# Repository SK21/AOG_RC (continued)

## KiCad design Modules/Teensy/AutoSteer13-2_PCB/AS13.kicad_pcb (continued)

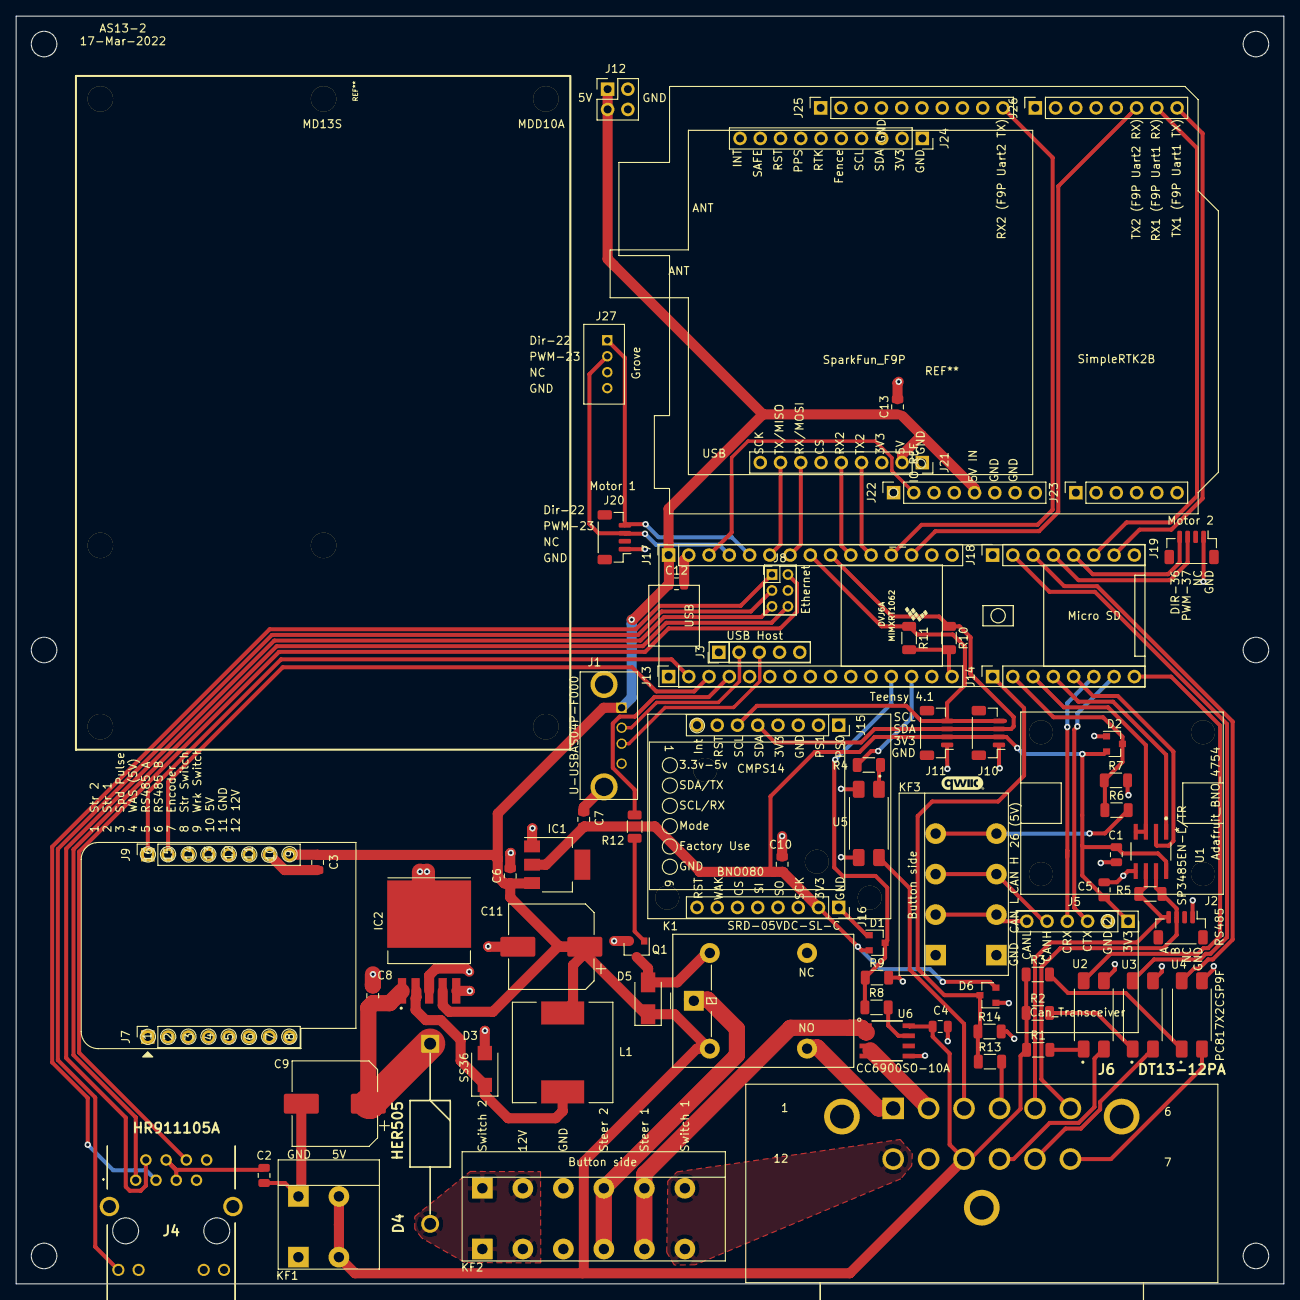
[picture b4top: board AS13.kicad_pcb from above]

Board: 2 copper layers, 159.0 x 159.0 mm, 82 parts (0 on the bottom side), 67 nets.

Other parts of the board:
  : MountingHole_3.2mm_M3
  #2,   #3,   #4,   #5,   #6: MountingHole_3.2mm_M3
--: Teensy 4.1; Teensy41_no_pins
M1: CMPS14; CMPS14_no_pins

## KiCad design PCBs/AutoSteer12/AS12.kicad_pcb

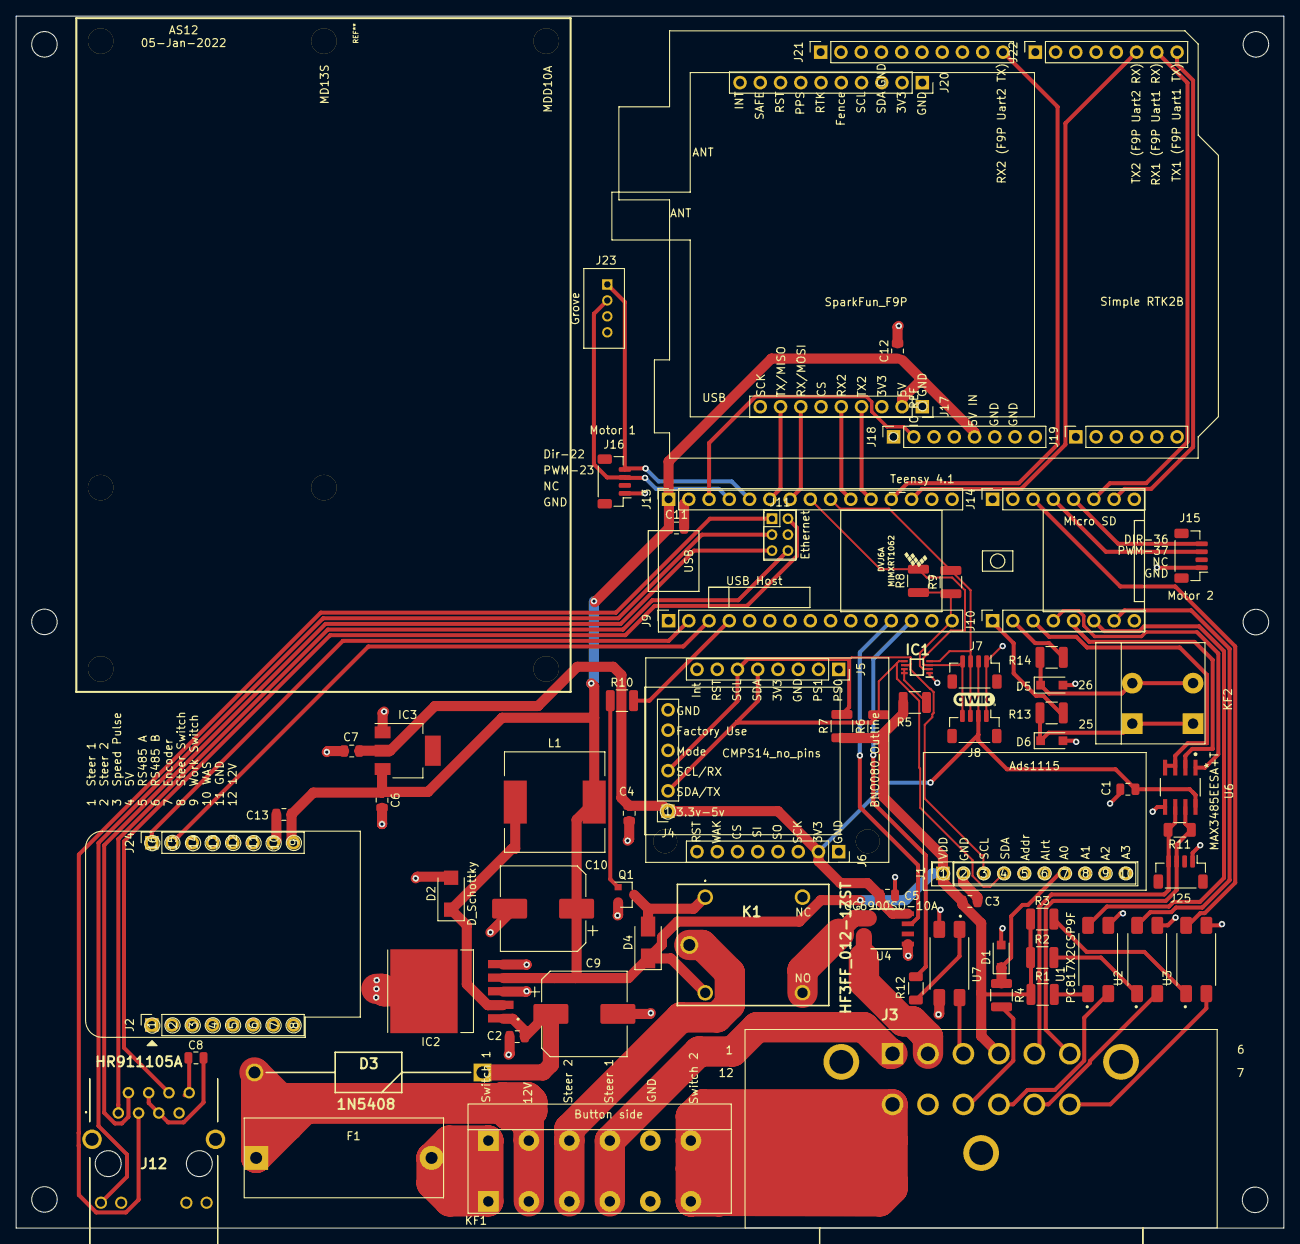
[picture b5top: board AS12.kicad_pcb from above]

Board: 2 copper layers, 159.0 x 152.0 mm, 81 parts (0 on the bottom side), 66 nets.

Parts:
 : MountingHole_3.2mm_M3
 #2,  #3,  #4,  #5,  #6: MountingHole_3.2mm_M3
--: Teensy 4.1; Teensy41_no_pins
C1, C3, C4, C5, C8, C11, C12, C13: 0.1uF; C_0805_2012Metric
C2: CL21B105KAFNNNE; C_0805_2012Metric
C6: 10uF; C_0805_2012Metric
C7: 22uF; C_0805_2012Metric
C9: RVT1V471M1010; CP_Elec_10x10.5
C10: RVT1V331M1010; CP_Elec_10x10.5
D1, D5, D6: Zener Diode; D_SOD-123F
D2: D_Schottky; SMA(DO-214AC)
D3: 1N5408; DO-201AD-28
D4: 1N4007; D_SMA
F1: Fuse; Fuse_Holder_C3131
IC1: PCA9306DCUR; SOP50P310X90-8N
IC2: XL2596; TO263-5L
IC3: AZ1117; SOT-223
J1: ADS1115; PinSocket_1x10_P2.54mm_Vertical
J2: WemosD1_left; PinSocket_1x08_P2.54mm_Vertical
J3: DT13-12PA; DT1312PA
J4: CMPS14; PinSocket_1x06_P2.54mm_Vertical
J5: BNO080_left; PinSocket_1x08_P2.54mm_Vertical
J6: BNO080_right; PinSocket_1x08_P2.54mm_Vertical
J7, J8: I2C-3V3; Qwic_vertical
J9, J13: Conn_01x15_Female; PinSocket_1x15_P2.54mm_Vertical
J10, J14: Conn_01x08_Female; PinSocket_1x08_P2.54mm_Vertical
J11: Teensy_Ethernet; PinHeader_2x03_P2.00mm_Vertical
J12: HR911105A
J15: Motor 2; Qwic_vertical
J16: Motor 1; Qwic_vertical
J17: SF_F9P_left; PinSocket_1x09_P2.54mm_Vertical
J18: ArduSimple_tl; PinSocket_1x08_P2.54mm_Vertical
J19: ArduSimple_bl; PinSocket_1x06_P2.54mm_Vertical
J20: SF_F9P_right; PinSocket_1x10_P2.54mm_Vertical
J21: ArduSimple_tr; PinSocket_1x10_P2.54mm_Vertical
J22: ArduSimple_br; PinSocket_1x08_P2.54mm_Vertical
J23: Grove
J24: WemosD1_right; PinSocket_1x08_P2.54mm_Vertical
J25: RS485; Qwic_vertical
K1: HF3FF_012-1ZST; HF3FF0121ZST
KF1: KF142V-5.0-6P; KF142V-5.08-6P
KF2: KF142V-5.0-2P; KF142V-5.08-2P
L1: SMDRI127-330MT; TMPA1265SP-101MN-D
M1: CMPS14_no_pins
Q1: BC847; SOT-23
R1, R2, R3, R4, R13, R14: 200; R_1210_3225Metric
R5: 200K; R_1210_3225Metric
R6, R7: 341; R_1210_3225Metric
R8, R9: 217; R_1210_3225Metric
R10: 1K; R_1210_3225Metric
R11: 120; R_1206_3216Metric
R12: 100; R_1206_3216Metric
U1, U2, U3, U7: PC817X2CSP9F; SOIC254P960X420-4N
U4: CC6900SO-10A; SOIC127P600X175-8N
U6: MAX3485EESA+T; Maxim_Integrated-S8-2-0-P-MFG

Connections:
GND: C1.2, C2.2, C3.2, C4.2, C5.2, C6.2, C7.2, C8.2, C9.2, C10.2, C11.2, C12.2, C13.2, D1.2, D2.2, D5.2, D6.2, IC1.1, IC2.3, IC2.5, IC2.6, IC3.1, J1.2, J1.5, J3.11, J4.6, J6.1, J7.1, J8.1, J9.1, J11.4, J12.8, J12.10, J13.2, J13.15, J15.1, J16.1, J17.1, J18.6, J18.7, J21.4, J23.4, J24.7, J25.1, KF1.5, Q1.2, U1.3, U2.3, U3.3, U4.5, U6.5, U7.2, U7.3
unnamed: C1.1, C4.1, C5.1, C7.1, IC3.2, J4.1, J6.2, J7.2, J8.2, U4.8, U6.8
unnamed: C2.1, C9.1, D3.1, IC2.1
unnamed: C8.1, J12.4, J12.5
unnamed: C3.1, C6.1, C10.1, C11.1, C12.1, C13.1, D4.1, IC2.4, IC3.3, J1.1, J3.4, J13.1, J17.2, J18.5, J24.8, K1.3, L1.2, R1.1, R2.1, R3.1, R5.1, R6.1, R7.1
unnamed: D1.1, J1.7, R4.1
unnamed: D2.1, IC2.2, L1.1
unnamed: D3.2, F1.1, KF1.2
unnamed: D4.2, K1.1, Q1.3
unnamed: D5.1, KF2.2, R14.1
unnamed: D6.1, KF2.1, R13.1
unnamed: F1.2, KF1.1
unnamed: IC1.2, J9.15, R8.1, R9.1
unnamed: IC1.3, J7.4, J8.4, J13.8, R8.2
unnamed: IC1.4, J7.3, J8.3, J13.9, R9.2
unnamed: IC1.5, J1.4, J4.2, J5.5, R6.2
unnamed: IC1.6, J1.3, J4.3, J5.6, R7.2
unnamed: IC1.7, IC1.8, R5.2
unnamed: J3.1, KF1.4
unnamed: J3.2, U4.3, U4.4
unnamed: J3.3, U7.4
unnamed: J3.7, U3.2
unnamed: J3.8, U2.2
unnamed: J3.9, U1.2
unnamed: J3.10, R4.2
unnamed: J3.12, KF1.6
unnamed: J9.4, R10.2
unnamed: J9.12, U4.7
unnamed: J9.13, R12.1
unnamed: J10.1, R13.2
unnamed: J10.2, R14.2
unnamed: J10.3, U6.3, U6.4
unnamed: J10.4, U6.1
unnamed: J10.5, U6.2
unnamed: J10.6, U1.4
unnamed: J10.7, U2.4
unnamed: J11.1, J12.3
unnamed: J11.2, J12.6
unnamed: J11.3, J12.9
unnamed: J11.5, J12.2
unnamed: J11.6, J12.1
unnamed: J13.3, J18.2
unnamed: J13.4, J16.3, J23.2
unnamed: J13.5, J16.4, J23.1
unnamed: J13.6, J17.8
unnamed: J13.7, J17.7
unnamed: J13.10, J17.5
unnamed: J13.11, J17.4
unnamed: J13.12, J21.10
unnamed: J13.13, J22.6
unnamed: J14.3, U3.4
unnamed: J14.4, J15.3
unnamed: J14.5, J15.4
unnamed: J14.6, J22.7
unnamed: J14.7, J22.8
unnamed: J9.2, J24.1
unnamed: J9.3, J24.2
unnamed: J3.6, J25.3, R11.1, U6.7
unnamed: J3.5, J25.4, R11.2, U6.6
unnamed: K1.2, KF1.3
unnamed: K1.4, U4.1, U4.2
unnamed: Q1.1, R10.1
unnamed: R1.2, U1.1
unnamed: R2.2, U2.1
unnamed: R3.2, U3.1
unnamed: R12.2, U7.1

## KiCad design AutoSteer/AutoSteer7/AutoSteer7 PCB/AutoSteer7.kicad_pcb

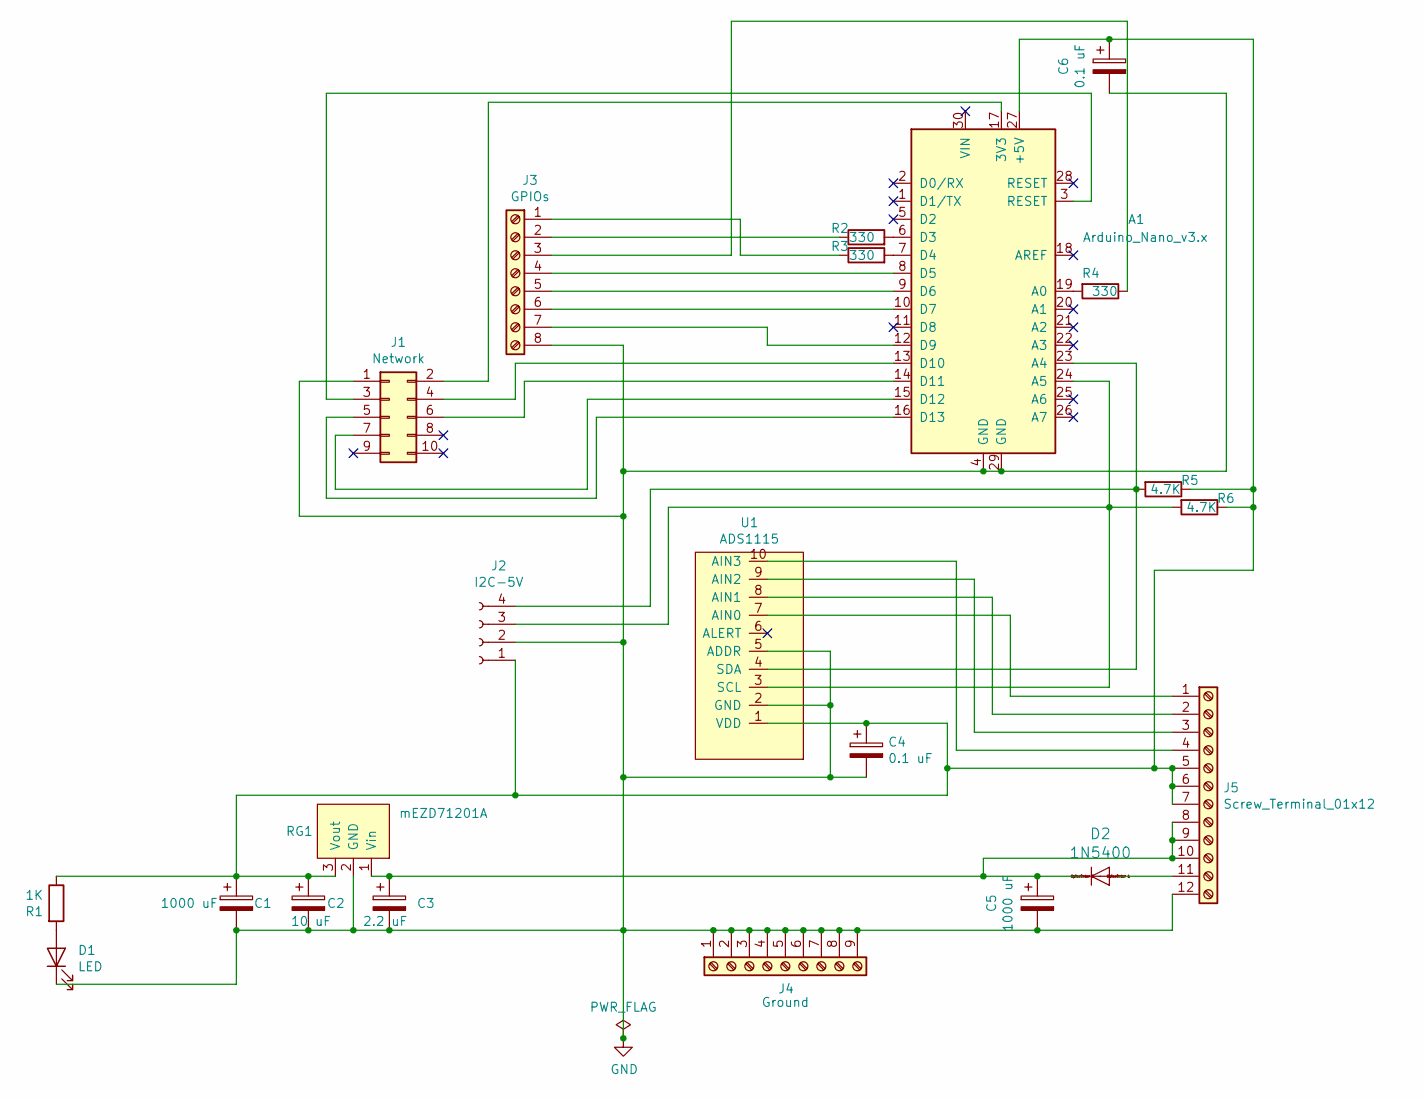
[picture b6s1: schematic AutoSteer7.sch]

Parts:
A1: Arduino_Nano_v3.x; Arduino_Nano
C1, C5: 1000 uF; CP_Radial_D10.0mm_P5.00mm
C2: 10 uF; C_Disc_D5.0mm_W2.5mm_P2.50mm
C3: 2.2 uF; C_Disc_D5.0mm_W2.5mm_P2.50mm
C4, C6: 0.1 uF; C_Disc_D5.0mm_W2.5mm_P2.50mm
D1: LED; LED_D3.0mm
D2: 1N5400
J1: Network; PinSocket_2x05_P2.54mm_Vertical
J2: I2C-5V; PinSocket_1x04_P2.54mm_Vertical
J3: GPIOs; TerminalBlock_Phoenix_PT-1,5-8-5.0-H_1x08_P5.00mm_Horizontal
J4: Ground; TerminalBlock_Phoenix_PT-1,5-9-5.0-H_1x09_P5.00mm_55degrees
J5: Screw_Terminal_01x12; TerminalBlock_Phoenix_PT-1,5-12-5.0-H_1x12_P5.00mm_Horizont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
R1: 1K; R_Axial_DIN0207_L6.3mm_D2.5mm_P10.16mm_Horizontal
R2, R3, R4: 330; R_Axial_DIN0207_L6.3mm_D2.5mm_P10.16mm_Horizontal
R5, R6: 4.7K; R_Axial_DIN0207_L6.3mm_D2.5mm_P10.16mm_Horizontal
RG1: mEZD71201A
U1: ADS1115; ads1115

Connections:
GND: A1.4 (GND), A1.29 (GND), C1.2, C2.2, C3.2, C4.2, C5.2, C6.2, D1.1 (K), J1.1, J2.2, J3.8, J4.1, J4.2, J4.3, J4.4, J4.5, J4.6, J4.7, J4.8, J4.9, J5.12, RG1.2 (GND), U1.2 (GND), U1.5 (ADDR)
unnamed: A1.3 (RESET), J1.3
unnamed: A1.6 (D3), R2.2
unnamed: A1.7 (D4), R3.2
unnamed: A1.8 (D5), J3.4
unnamed: A1.9 (D6), J3.5
unnamed: A1.10 (D7), J3.6
unnamed: A1.12 (D9), J3.7
unnamed: A1.13 (D10), J1.4
unnamed: A1.14 (D11), J1.6
unnamed: A1.15 (D12), J1.7
unnamed: A1.16 (D13), J1.5
unnamed: A1.17 (3V3), J1.2
unnamed: A1.19 (A0), R4.2
unnamed: A1.23 (A4), J2.4, R5.2, U1.4 (SDA)
unnamed: A1.24 (A5), J2.3, R6.2, U1.3 (SCL)
unnamed: A1.27 (+5V), C1.1, C2.1, C4.1, C6.1, J2.1, J5.5, J5.6, J5.7, R1.1, R5.1, R6.1, RG1.3 (Vout), U1.1 (VDD)
unnamed: C3.1, C5.1, D2.C, J5.8, J5.9, J5.10, RG1.1 (Vin)
unnamed: D1.2 (A), R1.2
unnamed: D2.A, J5.11
unnamed: J3.1, R3.1
unnamed: J3.2, R2.1
unnamed: J3.3, R4.1
unnamed: J5.1, U1.7 (AIN0)
unnamed: J5.2, U1.8 (AIN1)
unnamed: J5.3, U1.9 (AIN2)
unnamed: J5.4, U1.10 (AIN3)

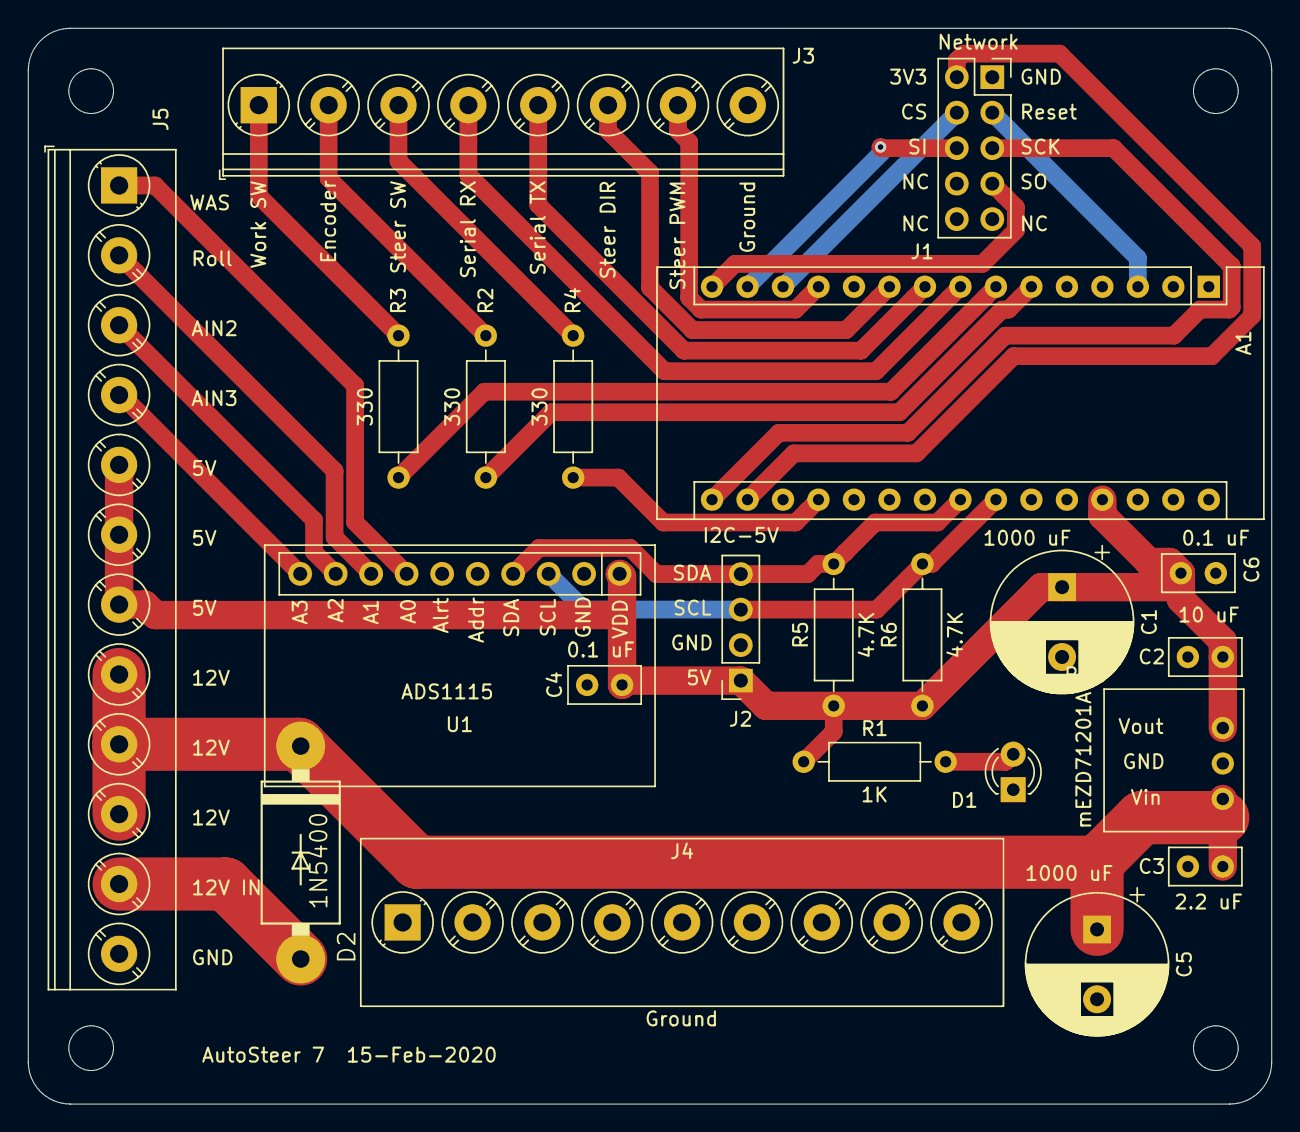
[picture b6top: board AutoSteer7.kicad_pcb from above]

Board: 2 copper layers, 89.0 x 77.0 mm, 22 parts (0 on the bottom side), 27 nets.

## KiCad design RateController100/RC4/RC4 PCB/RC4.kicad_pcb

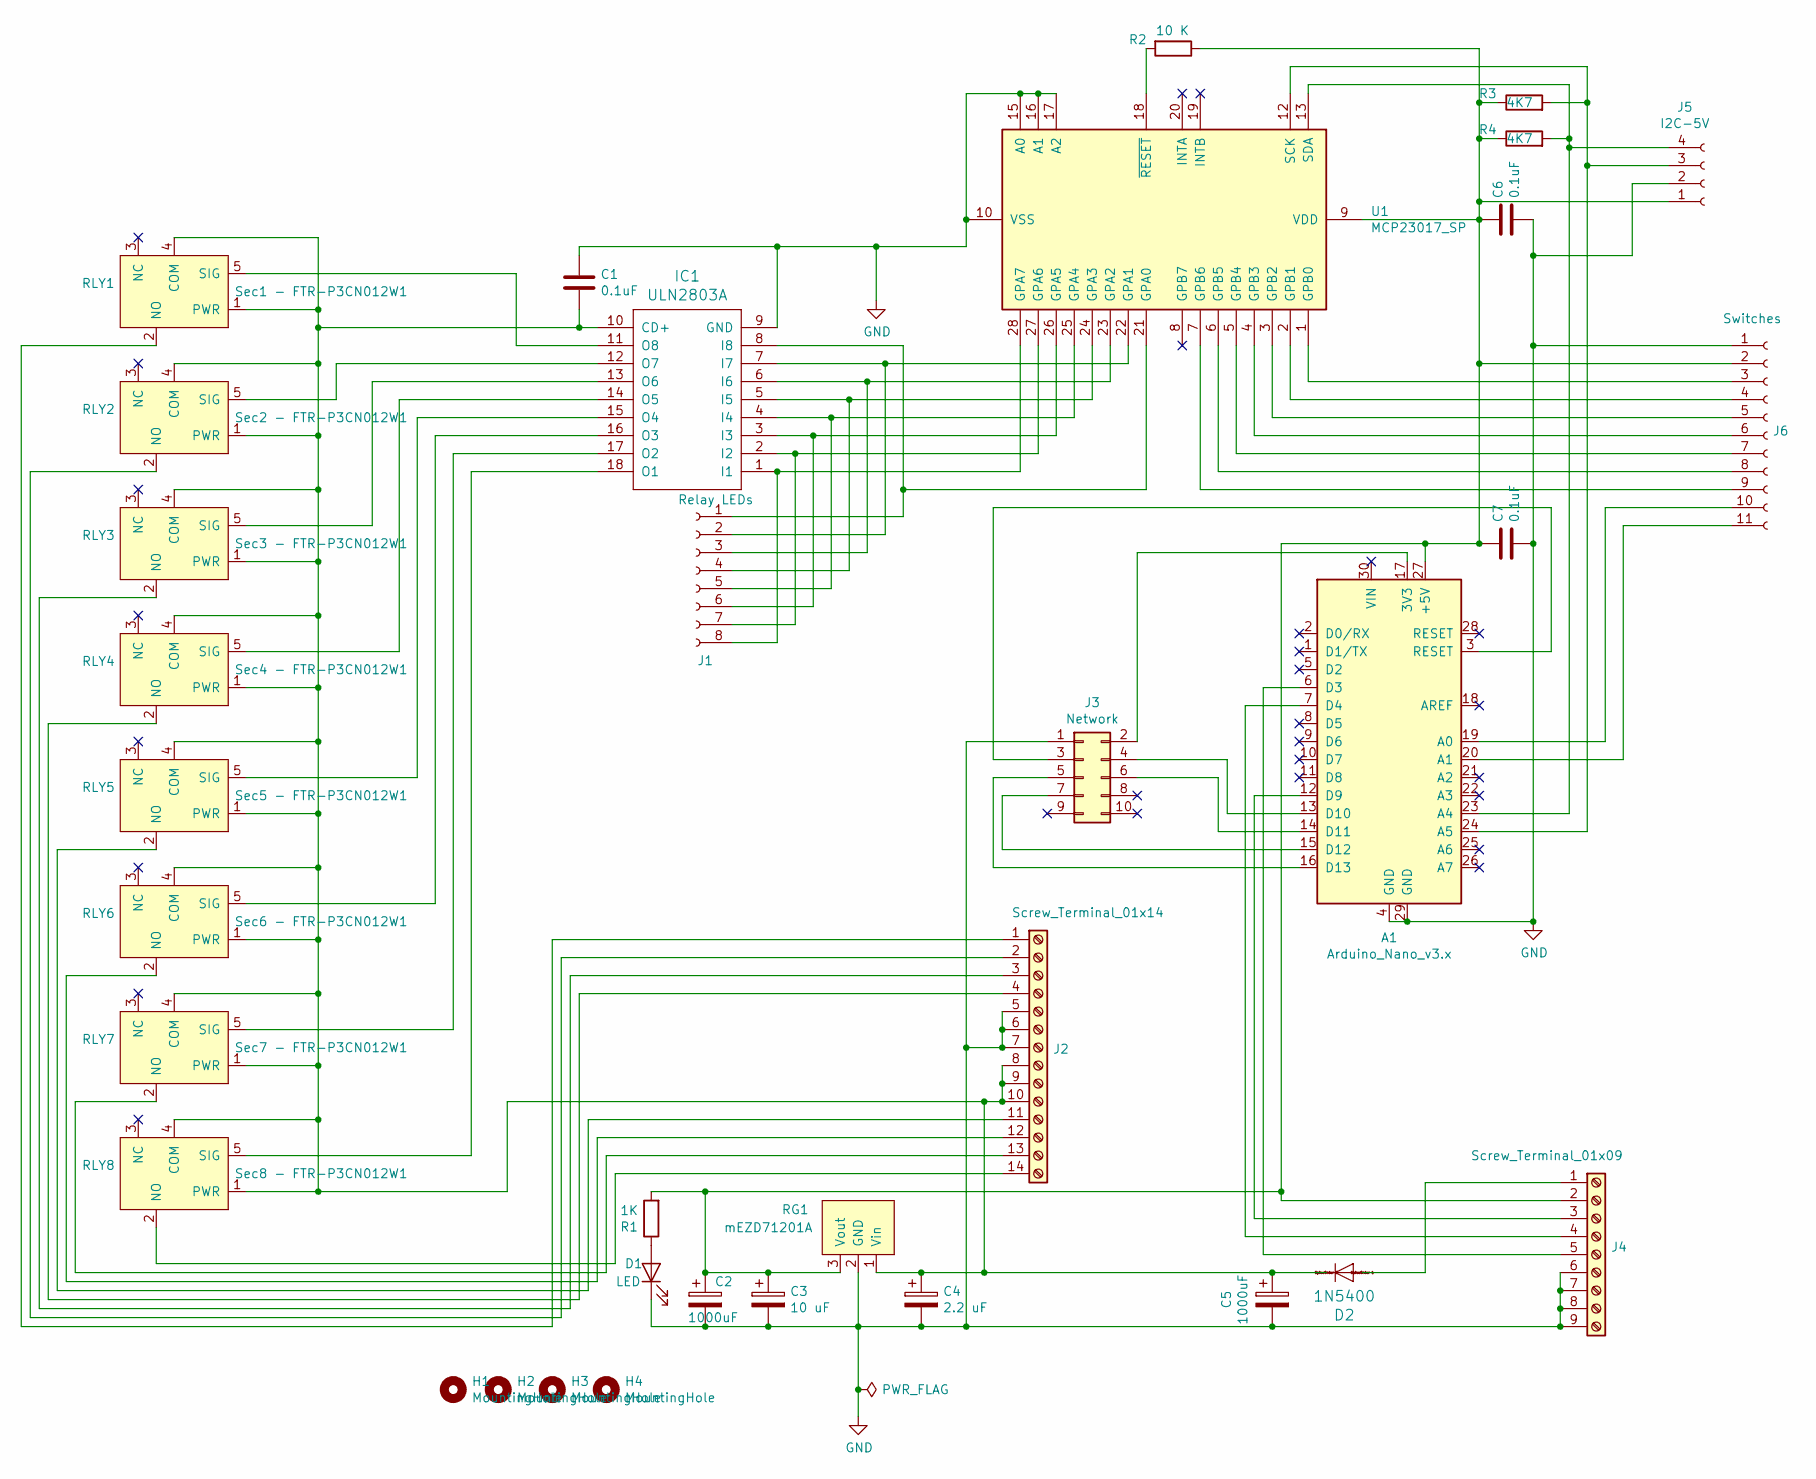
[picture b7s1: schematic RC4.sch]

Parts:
A1: Arduino_Nano_v3.x; Arduino_Nano
C1, C6, C7: 0.1uF; C_Disc_D5.0mm_W2.5mm_P2.50mm
C2, C5: 1000uF; CP_Radial_D10.0mm_P5.00mm
C3: 10 uF; C_Disc_D5.0mm_W2.5mm_P2.50mm
C4: 2.2 uF; C_Disc_D5.0mm_W2.5mm_P2.50mm
D1: LED; LED_D3.0mm
D2: 1N5400
H1, H2, H3, H4: MountingHole; MountingHole_3.2mm_M3
IC1: ULN2803A; DIL18
J1: Relay LEDs; PinHeader_1x08_P2.54mm_Vertical
J2: Screw_Terminal_01x14; TerminalBlock_Phoenix_MKDS-1,5-14_1x14_P5.00mm_Horizontal
J3: Network; PinSocket_2x05_P2.54mm_Vertical
J4: Screw_Terminal_01x09; TerminalBlock_Phoenix_PT-1,5-9-5.0-H_1x09_P5.00mm_Horizontal
J5: I2C-5V; PinSocket_1x04_P2.54mm_Vertical
J6: Switches; PinHeader_1x11_P2.54mm_Vertical
R1: 1K; R_Axial_DIN0207_L6.3mm_D2.5mm_P10.16mm_Horizontal
R2: 10 K; R_Axial_DIN0207_L6.3mm_D2.5mm_P10.16mm_Horizontal
R3, R4: 4K7; R_Axial_DIN0207_L6.3mm_D2.5mm_P10.16mm_Horizontal
RG1: mEZD71201A
RLY1: Sec1 - FTR-P3CN012W1; FTR-P3_Relay
RLY2: Sec2 - FTR-P3CN012W1; FTR-P3_Relay
RLY3: Sec3 - FTR-P3CN012W1; FTR-P3_Relay
RLY4: Sec4 - FTR-P3CN012W1; FTR-P3_Relay
RLY5: Sec5 - FTR-P3CN012W1; FTR-P3_Relay
RLY6: Sec6 - FTR-P3CN012W1; FTR-P3_Relay
RLY7: Sec7 - FTR-P3CN012W1; FTR-P3_Relay
RLY8: Sec8 - FTR-P3CN012W1; FTR-P3_Relay
U1: MCP23017_SP; DIP-28_W7.62mm

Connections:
GND: A1.4 (GND), A1.29 (GND), C1.1, C2.2, C3.2, C4.2, C5.2, C6.2, C7.2, D1.1 (K), IC1.9 (GND), J2.5, J2.6, J2.7, J3.1, J4.6, J4.7, J4.8, J4.9, J5.2, J6.1, RG1.2 (GND), U1.10 (VSS), U1.15 (A0), U1.16 (A1), U1.17 (A2)
unnamed: A1.3 (RESET), J3.3
unnamed: A1.6 (D3), J4.5
unnamed: A1.7 (D4), J4.4
unnamed: A1.12 (D9), J4.3
unnamed: A1.13 (D10), J3.4
unnamed: A1.14 (D11), J3.6
unnamed: A1.15 (D12), J3.7
unnamed: A1.16 (D13), J3.5
unnamed: A1.17 (3V3), J3.2
unnamed: A1.19 (A0), J6.10
unnamed: A1.20 (A1), J6.11
unnamed: A1.23 (A4), J5.4, R4.2, U1.13 (SDA)
unnamed: A1.24 (A5), J5.3, R3.2, U1.12 (SCK)
unnamed: A1.27 (+5V), C2.1, C3.1, C6.1, C7.1, J4.2, J5.1, J6.2, R1.2, R2.1, R3.1, R4.1, RG1.3 (Vout), U1.9 (VDD)
unnamed: C1.2, C4.1, C5.1, D2.C, IC1.10 (CD+), J2.8, J2.9, J2.10, RG1.1 (Vin), RLY1.1 (PWR), RLY1.4 (COM), RLY2.1 (PWR), RLY2.4 (COM), RLY3.1 (PWR), RLY3.4 (COM), RLY4.1 (PWR), RLY4.4 (COM), RLY5.1 (PWR), RLY5.4 (COM), RLY6.1 (PWR), RLY6.4 (COM), RLY7.1 (PWR), RLY7.4 (COM), RLY8.1 (PWR), RLY8.4 (COM)
unnamed: D1.2 (A), R1.1
unnamed: D2.A, J4.1
unnamed: IC1.1 (I1), J1.8, U1.28 (GPA7)
unnamed: IC1.2 (I2), J1.7, U1.27 (GPA6)
unnamed: IC1.3 (I3), J1.6, U1.26 (GPA5)
unnamed: IC1.4 (I4), J1.5, U1.25 (GPA4)
unnamed: IC1.5 (I5), J1.4, U1.24 (GPA3)
unnamed: IC1.6 (I6), J1.3, U1.23 (GPA2)
unnamed: IC1.7 (I7), J1.2, U1.22 (GPA1)
unnamed: IC1.8 (I8), J1.1, U1.21 (GPA0)
unnamed: IC1.11 (O8), RLY1.5 (SIG)
unnamed: IC1.12 (O7), RLY2.5 (SIG)
unnamed: IC1.13 (O6), RLY3.5 (SIG)
unnamed: IC1.14 (O5), RLY4.5 (SIG)
unnamed: IC1.15 (O4), RLY5.5 (SIG)
unnamed: IC1.16 (O3), RLY6.5 (SIG)
unnamed: IC1.17 (O2), RLY7.5 (SIG)
unnamed: IC1.18 (O1), RLY8.5 (SIG)
unnamed: J2.1, RLY1.2 (NO)
unnamed: J2.2, RLY2.2 (NO)
unnamed: J2.3, RLY3.2 (NO)
unnamed: J2.4, RLY4.2 (NO)
unnamed: J2.11, RLY5.2 (NO)
unnamed: J2.12, RLY6.2 (NO)
unnamed: J2.13, RLY7.2 (NO)
unnamed: J2.14, RLY8.2 (NO)
unnamed: J6.3, U1.1 (GPB0)
unnamed: J6.4, U1.2 (GPB1)
unnamed: J6.5, U1.3 (GPB2)
unnamed: J6.6, U1.4 (GPB3)
unnamed: J6.7, U1.5 (GPB4)
unnamed: J6.8, U1.6 (GPB5)
unnamed: J6.9, U1.7 (GPB6)
unnamed: R2.2, U1.18 (~RESET~)

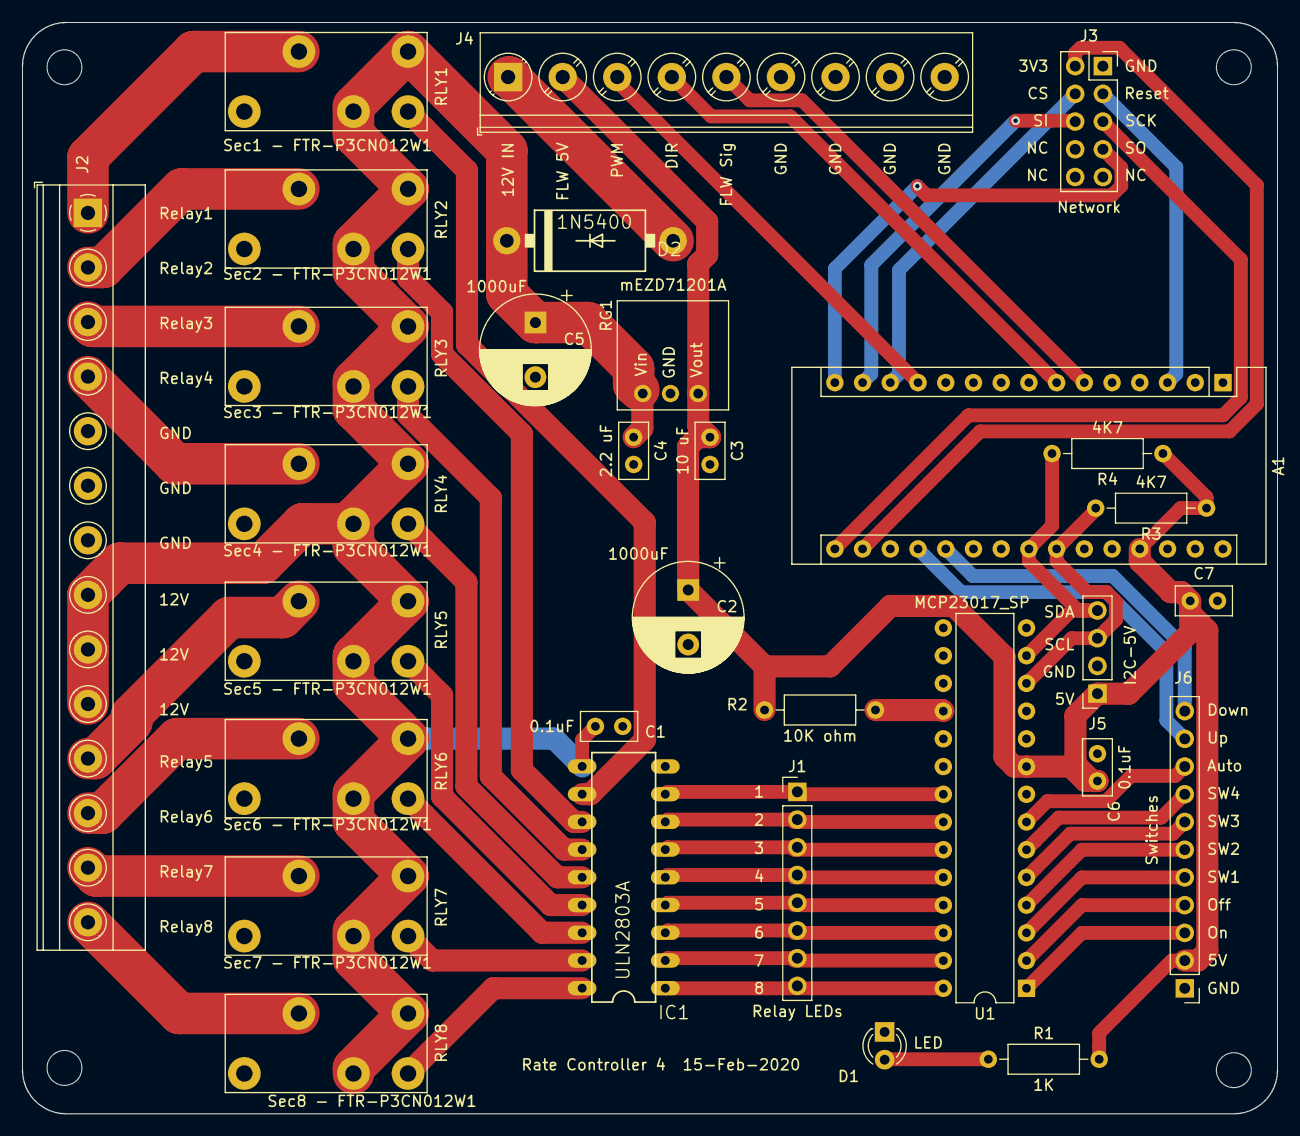
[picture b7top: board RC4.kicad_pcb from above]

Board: 2 copper layers, 115.0 x 100.0 mm, 35 parts (0 on the bottom side), 50 nets.

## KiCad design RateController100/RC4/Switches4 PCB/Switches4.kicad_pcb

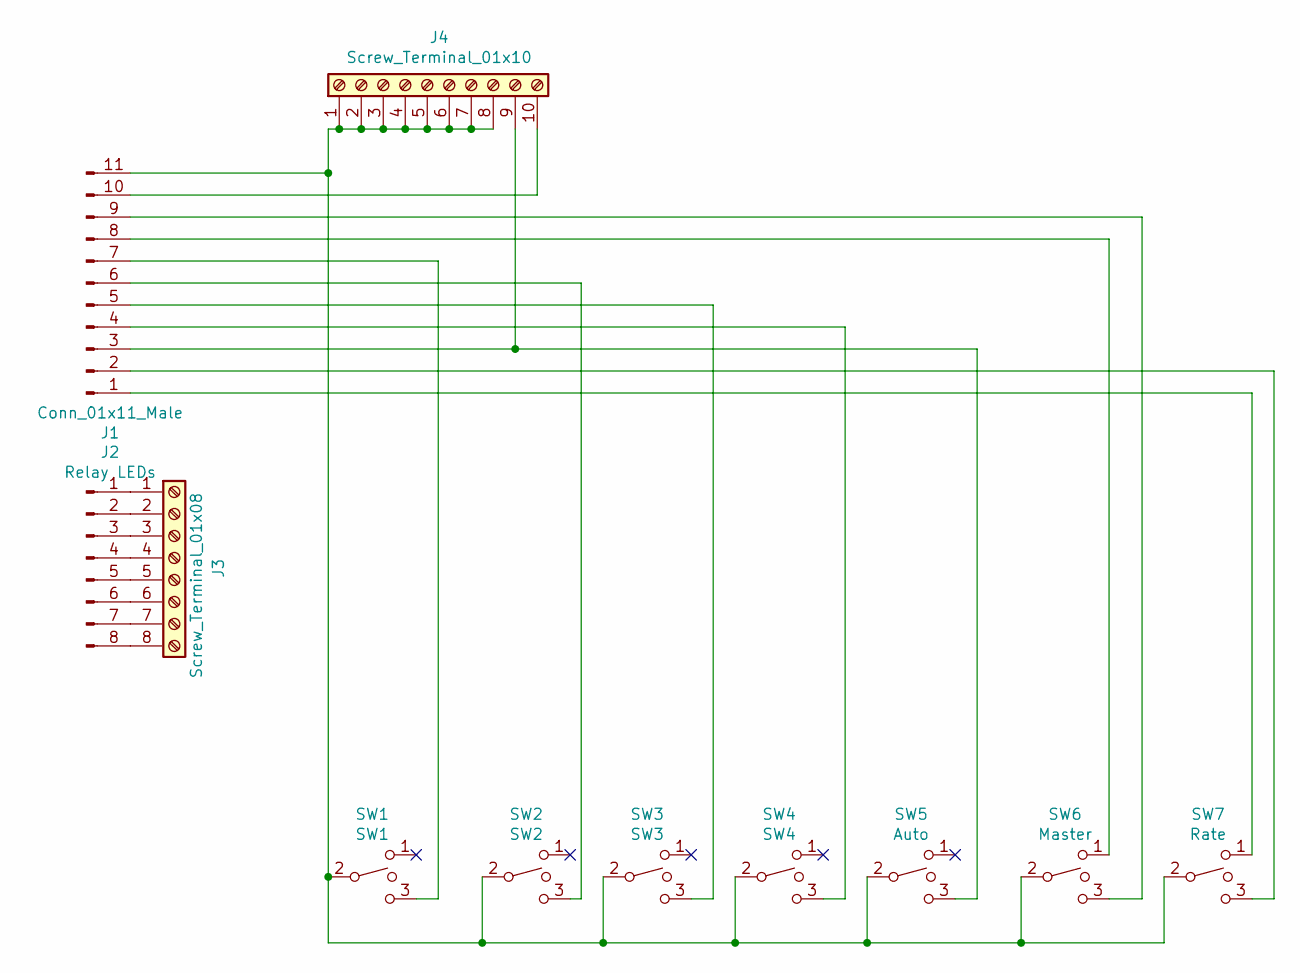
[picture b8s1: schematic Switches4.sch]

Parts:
J1: Conn_01x11_Male; PinHeader_1x11_P2.54mm_Horizontal
J2: Relay LEDs; PinHeader_1x08_P2.54mm_Horizontal
J3: Screw_Terminal_01x08; TerminalBlock_Phoenix_PT-1,5-8-5.0-H_1x08_P5.00mm_Horizontal
J4: Screw_Terminal_01x10; TerminalBlock_Phoenix_PT-1,5-10-5.0-H_1x10_P5.00mm_Horizont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
SW1: SW1; Mini_Toggle_3pin
SW2: SW2; Mini_Toggle_3pin
SW3: SW3; Mini_Toggle_3pin
SW4: SW4; Mini_Toggle_3pin
SW5: Auto; Mini_Toggle_3pin
SW6: Master; Mini_Toggle_3pin
SW7: Rate; Mini_Toggle_3pin

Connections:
unnamed: J1.1, SW7.1
unnamed: J1.2, SW7.3
unnamed: J1.3, J4.9, SW5.3
unnamed: J1.4, SW4.3
unnamed: J1.5, SW3.3
unnamed: J1.6, SW2.3
unnamed: J1.7, SW1.3
unnamed: J1.8, SW6.1
unnamed: J1.9, SW6.3
unnamed: J1.10, J4.10
unnamed: J1.11, J4.1, J4.2, J4.3, J4.4, J4.5, J4.6, J4.7, J4.8, SW1.2, SW2.2, SW3.2, SW4.2, SW5.2, SW6.2, SW7.2
unnamed: J2.1, J3.1
unnamed: J2.2, J3.2
unnamed: J2.3, J3.3
unnamed: J2.4, J3.4
unnamed: J2.5, J3.5
unnamed: J2.6, J3.6
unnamed: J2.7, J3.7
unnamed: J2.8, J3.8

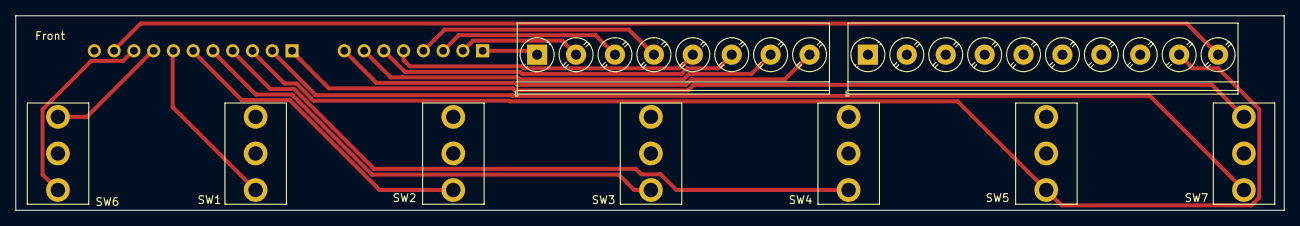
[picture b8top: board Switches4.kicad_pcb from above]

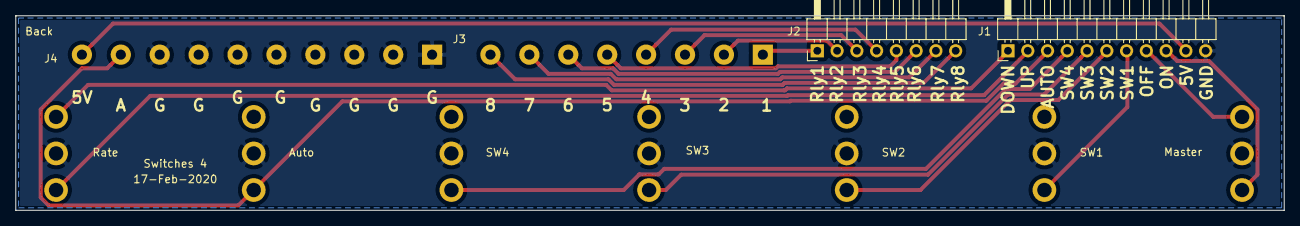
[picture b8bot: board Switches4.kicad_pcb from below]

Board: 2 copper layers, 163.0 x 25.0 mm, 11 parts (2 on the bottom side), 19 nets.

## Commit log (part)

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2026-02-28 fix pgn time
2026-02-28 fix default for remote relay
2026-02-28 fix highlight bug
2026-02-28 fix highlight
2026-02-28 module simulator
2026-02-28 set sim screen position
2026-02-28 dual sim
2026-03-01 fix dual sim
2026-03-01 add controls to sim
2026-03-01 remove old code
2026-03-01 sim products
2026-03-01 fix sim
2026-03-02 clean up esp32 code
2026-03-14 add user manual
2026-03-15 update help pages and user manual
2026-03-29 fix udp share
2026-03-30 fix esp32 ota update
2026-03-30 update parcels
2026-03-30 create fielddatamanager
2026-03-31 update parcelmanage for a single elevation file
2026-03-31 add frmMap tab
2026-03-31 require a job on startup
2026-04-01 fix legend base value
2026-04-01 Improve pin assignment to consider only the PINs that are supported by the PCB.
2026-04-02 fix profile load bug
2026-04-03 update main form display
2026-04-03 update main form
2026-04-03 fix missing reference file
2026-04-03 change tank indicator
2026-04-04 change bar graph
2026-04-04 update to remote relays
2026-04-04 update tank display
2026-04-05 fix alarm bug
2026-04-05 prescription per job
2026-04-05 fix job reference for prescription
2026-04-05 update yield overlay creator
2026-04-06 Rx selection
2026-04-06 new prescription
2026-04-06 copy prescription
2026-04-06 import prescription
2026-04-06 fix import
2026-04-06 fix prescription files
2026-04-06 fix export
2026-04-06 export prescription fix
2026-04-07 clean up file handling
2026-04-07 manual adjustment
2026-04-07 adjust rate with master off
2026-04-08 rate switch responsiveness
2026-04-08 update on-screen switches
2026-04-08 update help files
2026-04-08 update bug fix
2026-04-08 fix motor bug
2026-04-08 RCRestore track location
2026-04-09 frmMain minimize on Map max
2026-04-09 remove FieldDataManager
2026-04-09 kml file import
2026-04-09 fix file control
2026-04-09 Comm menu
2026-04-09 move frmMenuComm
2026-04-09 edit frmMenuComm
2026-04-09 add diagnostics button
2026-04-09 update frmMenuComm
2026-04-09 cleanup boards form
2026-04-09 cleanup frmMenuOptions
2026-04-09 restart can on settings change
2026-04-09 fix frmMenuHelp
2026-04-11 fix fans
2026-04-12 fix elevation display
2026-04-12 polygon elevation
2026-04-12 change resolution
2026-04-12 productivity button
2026-04-13 EC and NVI
2026-04-13 file management
2026-04-13 remove nvi
2026-04-13 EC files
2026-04-13 zone list
2026-04-14 fix zone line
2026-04-14 zone list checkbox
2026-04-14 fix zone list
2026-04-14 check for duplicate zone names
2026-04-15 frmCreateZones
2026-04-15 add frmCreateZones events
2026-04-15 fix frmCreateZones
2026-04-15 frmCreateZones highlighting
2026-04-16 import aog field boundaries
2026-04-16 static class for kml files
2026-04-16 update productivity zone creator
2026-04-16 update zone generation
2026-04-16 show status 3wire
2026-04-16 udpate activity log
2026-04-16 edit manual rate adjustment
2026-04-16 board reset button
2026-04-16 fix zone generation
2026-04-16 update frmCreateZones
2026-04-16 update status pgn
2026-04-16 fix debug buttons
2026-04-16 fix master relay/switch
2026-04-17 update manual
2026-04-17 bug fix on module config
2026-04-17 fix manual rate adjust
2026-04-18 fix switches
2026-04-18 add pressure alarm
2026-04-18 edit speed from aog
2026-04-18 fix zone create
2026-04-18 fix kml import
2026-04-21 remove master control relay only mode
2026-04-21 remove relay status
2026-04-21 change relay modes
2026-04-21 create clsRateAdjustController
2026-04-22 refactor clsSectionControl
2026-04-22 refactor clsrelays
2026-04-22 fix menuPrimed
2026-04-22 fix prime mode
2026-04-23 fix hydraulic relays
2026-04-23 re-order relay combobox
2026-04-23 FlowMaster
2026-04-24 update FlowMaster
2026-04-24 update pgn32501
2026-04-24 fix frmMenuRelays reset
2026-04-24 update language
2026-04-24 update help
2026-04-24 sort relays
2026-04-25 update module status
2026-04-30 change data folder
2026-04-30 fix change data folder
2026-04-30 start minimized
2026-05-03 clean up data folder handling
2026-05-03 fix comboclose valve workflow
2026-05-03 fix comboclose bug
2026-05-04 fix rate adjust
2026-05-05 prevent divide by 0
2026-05-05 add esp32 files
2026-05-11 fix large zone imports
2026-05-11 print zone list
2026-05-12 fix map zones
2026-05-12 fix import zones
2026-05-15 xml import
2026-05-15 buggy imports
2026-05-15 fix shapefile import
2026-05-16 fix xml import
2026-05-16 fix xml import again
2026-05-16 save prescripition product settings
2026-05-18 edit vt files
2026-05-18 cleanup
2026-06-02 test oscillation damper
2026-06-02 fix date
2026-06-10 fix mini save position
2026-06-10 fix show jobs at startup
2026-06-10 increase integral, add damper code to esp32 and nano
2026-06-10 remove reset button from rate page
2026-06-10 fix auto switch defaults
2026-06-10 split up the comm page
2026-06-10 clarify jobs form
2026-06-10 user defined number of switches
2026-06-19 add pid data logging to the teensy firmware
2026-06-19 add pid data logging to the app
2026-06-20 fix master off bug, update pid data logging
2026-06-21 integral, pid, logging update
2026-06-21 update app
2026-06-21 fix min upm
2026-06-21 min upm hint
2026-06-22 max pressure control, rate flow sample window
2026-06-22 use sample window instead of pulse count
2026-06-22 floor sample count of 5
2026-06-25 fix min upm scaling
2026-06-26 linear scaled Kp/Ki
2026-06-26 code change doc
2026-06-26 pcb text ID
2026-06-26 can code for pcb text ID
2026-06-27 add firmware ID to log
